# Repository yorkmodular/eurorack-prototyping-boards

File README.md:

## Eurorack module prototyping boards

A range of boards to aid the design and construction of Eurorack modules - inspired by the 'perma proto-boards' offered by the likes of AdaFruit et.al.

Three sizes are offered:

- `small` is roughly equivalent to a mini 170pt breadboard. However, unlike mini breadboards, these do have power rails (see below). Overall size is 57.2 x 64mm
- `medium` is equivalent to a half-size (400pt) breadboard. Overall size is 60.4 x 94.7mm
- `large` is equivalent to a full-size (800pt) breadboard. Note that this is far too large to be fitted in a typical Eurorack case although it could be used for 'desktop' style modules. Users of other formats may find it useful too. Overall size is 60.4 x 171.4mm.

These boards differ from 'traditional' prototyping boards in a couple of ways:

- They have three power rails, rather than two. One for +12V, one for -12V and one for ground.
- There are M3 mounting holes at each corner.
- There are an additional couple of ground rails at the top of the board.
- Power is provided by a 10-pin Eurorack power header.

Electrically, the rows of 5 pads are connected in the same way as a 'traditional' breadboard. I am planning to make pad-per-hole versions of these boards 
available in the near future.

## Buy via OSHPark

These boards can be ordered via OSHPark using the links below - note that I don't receive any commission for purchases made this way.

- Small: https://oshpark.com/shared_projects/MuwHRMNy
- Medium: https://oshpark.com/shared_projects/Uu3mWM4d
- Large: https://oshpark.com/shared_projects/nStSqsz1

------------

[![CC BY-SA 4.0][cc-by-sa-shield]][cc-by-sa]

This work is licensed under a
[Creative Commons Attribution-ShareAlike 4.0 International License][cc-by-sa].

[![CC BY-SA 4.0][cc-by-sa-image]][cc-by-sa]

[cc-by-sa]: http://creativecommons.org/licenses/by-sa/4.0/
[cc-by-sa-image]: https://licensebuttons.net/l/by-sa/4.0/88x31.png
[cc-by-sa-shield]: https://img.shields.io/badge/License-CC%20BY--SA%204.0-lightgrey.svg

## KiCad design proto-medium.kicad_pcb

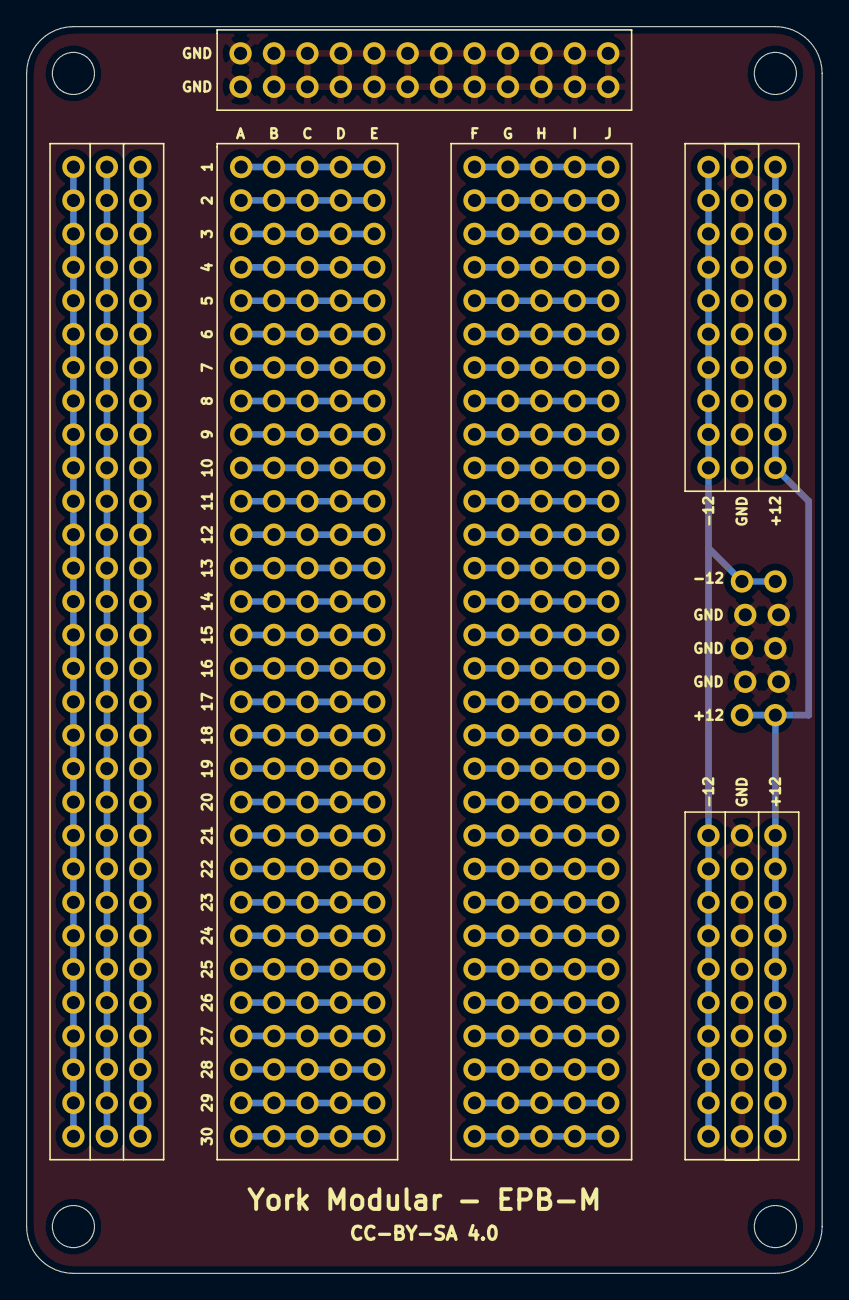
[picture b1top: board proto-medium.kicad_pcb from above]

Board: 2 copper layers, 60.5 x 94.7 mm, 26 parts (0 on the bottom side), 66 nets.

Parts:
H1, H2, H3, H4: MountingHole; MountingHole_3.2mm_M3
J1, J2, J3, J4, J5, J6, J7, J8, J9, J10, J11, J12, J13: Conn_01x30; PinHeader_1x30_P2.54mm_Vertical
J14: EURO_PWR_2x5; EURO-POWER
J15, J16, J17, J18, J19, J20: Conn_01x10; PinHeader_1x10_P2.54mm_Vertical
J21, J22: Conn_01x12; PinHeader_1x12_P2.54mm_Vertical

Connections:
+12V: J14.1, J14.2, J19.1, J19.2, J19.3, J19.4, J19.5, J19.6, J19.7, J19.8, J19.9, J19.10, J20.1, J20.2, J20.3, J20.4, J20.5, J20.6, J20.7, J20.8, J20.9, J20.10
-12V: J14.9, J14.10, J15.1, J15.2, J15.3, J15.4, J15.5, J15.6, J15.7, J15.8, J15.9, J15.10, J16.1, J16.2, J16.3, J16.4, J16.5, J16.6, J16.7, J16.8, J16.9, J16.10
GND: J14.3, J14.4, J14.5, J14.6, J14.7, J14.8, J17.1, J17.2, J17.3, J17.4, J17.5, J17.6, J17.7, J17.8, J17.9, J17.10, J18.1, J18.2, J18.3, J18.4, J18.5, J18.6, J18.7, J18.8, J18.9, J18.10, J21.1, J21.2, J21.3, J21.4, J21.5, J21.6, J21.7, J21.8, J21.9, J21.10, J21.11, J21.12, J22.1, J22.2, J22.3, J22.4, J22.5, J22.6, J22.7, J22.8, J22.9, J22.10, J22.11, J22.12
unnamed: J1.1, J2.1, J3.1, J4.1, J5.1
unnamed: J1.2, J2.2, J3.2, J4.2, J5.2
unnamed: J1.3, J2.3, J3.3, J4.3, J5.3
unnamed: J1.4, J2.4, J3.4, J4.4, J5.4
unnamed: J1.5, J2.5, J3.5, J4.5, J5.5
unnamed: J1.6, J2.6, J3.6, J4.6, J5.6
unnamed: J1.7, J2.7, J3.7, J4.7, J5.7
unnamed: J1.8, J2.8, J3.8, J4.8, J5.8
unnamed: J1.9, J2.9, J3.9, J4.9, J5.9
unnamed: J1.10, J2.10, J3.10, J4.10, J5.10
unnamed: J1.11, J2.11, J3.11, J4.11, J5.11
unnamed: J1.12, J2.12, J3.12, J4.12, J5.12
unnamed: J1.13, J2.13, J3.13, J4.13, J5.13
unnamed: J1.14, J2.14, J3.14, J4.14, J5.14
unnamed: J1.15, J2.15, J3.15, J4.15, J5.15
unnamed: J1.16, J2.16, J3.16, J4.16, J5.16
unnamed: J1.17, J2.17, J3.17, J4.17, J5.17
unnamed: J1.18, J2.18, J3.18, J4.18, J5.18
unnamed: J1.19, J2.19, J3.19, J4.19, J5.19
unnamed: J1.20, J2.20, J3.20, J4.20, J5.20
unnamed: J1.21, J2.21, J3.21, J4.21, J5.21
unnamed: J1.22, J2.22, J3.22, J4.22, J5.22
unnamed: J1.23, J2.23, J3.23, J4.23, J5.23
unnamed: J1.24, J2.24, J3.24, J4.24, J5.24
unnamed: J1.25, J2.25, J3.25, J4.25, J5.25
unnamed: J1.26, J2.26, J3.26, J4.26, J5.26
unnamed: J1.27, J2.27, J3.27, J4.27, J5.27
unnamed: J1.28, J2.28, J3.28, J4.28, J5.28
unnamed: J1.29, J2.29, J3.29, J4.29, J5.29
unnamed: J1.30, J2.30, J3.30, J4.30, J5.30
unnamed: J6.1, J7.1, J8.1, J9.1, J10.1
unnamed: J6.2, J7.2, J8.2, J9.2, J10.2
unnamed: J6.3, J7.3, J8.3, J9.3, J10.3
unnamed: J6.4, J7.4, J8.4, J9.4, J10.4
unnamed: J6.5, J7.5, J8.5, J9.5, J10.5
unnamed: J6.6, J7.6, J8.6, J9.6, J10.6
unnamed: J6.7, J7.7, J8.7, J9.7, J10.7
unnamed: J6.8, J7.8, J8.8, J9.8, J10.8
unnamed: J6.9, J7.9, J8.9, J9.9, J10.9
unnamed: J6.10, J7.10, J8.10, J9.10, J10.10
unnamed: J6.11, J7.11, J8.11, J9.11, J10.11
unnamed: J6.12, J7.12, J8.12, J9.12, J10.12
unnamed: J6.13, J7.13, J8.13, J9.13, J10.13
unnamed: J6.14, J7.14, J8.14, J9.14, J10.14
unnamed: J6.15, J7.15, J8.15, J9.15, J10.15
unnamed: J6.16, J7.16, J8.16, J9.16, J10.16
unnamed: J6.17, J7.17, J8.17, J9.17, J10.17
unnamed: J6.18, J7.18, J8.18, J9.18, J10.18
unnamed: J6.19, J7.19, J8.19, J9.19, J10.19
unnamed: J6.20, J7.20, J8.20, J9.20, J10.20
unnamed: J6.21, J7.21, J8.21, J9.21, J10.21
unnamed: J6.22, J7.22, J8.22, J9.22, J10.22
unnamed: J6.23, J7.23, J8.23, J9.23, J10.23
unnamed: J6.24, J7.24, J8.24, J9.24, J10.24
unnamed: J6.25, J7.25, J8.25, J9.25, J10.25
unnamed: J6.26, J7.26, J8.26, J9.26, J10.26
unnamed: J6.27, J7.27, J8.27, J9.27, J10.27
unnamed: J6.28, J7.28, J8.28, J9.28, J10.28
unnamed: J6.29, J7.29, J8.29, J9.29, J10.29
unnamed: J6.30, J7.30, J8.30, J9.30, J10.30
unnamed: J11.1, J11.2, J11.3, J11.4, J11.5, J11.6, J11.7, J11.8, J11.9, J11.10, J11.11, J11.12, J11.13, J11.14, J11.15, J11.16, J11.17, J11.18, J11.19, J11.20, J11.21, J11.22, J11.23, J11.24, J11.25, J11.26, J11.27, J11.28, J11.29, J11.30
unnamed: J12.1, J12.2, J12.3, J12.4, J12.5, J12.6, J12.7, J12.8, J12.9, J12.10, J12.11, J12.12, J12.13, J12.14, J12.15, J12.16, J12.17, J12.18, J12.19, J12.20, J12.21, J12.22, J12.23, J12.24, J12.25, J12.26, J12.27, J12.28, J12.29, J12.30
unnamed: J13.1, J13.2, J13.3, J13.4, J13.5, J13.6, J13.7, J13.8, J13.9, J13.10, J13.11, J13.12, J13.13, J13.14, J13.15, J13.16, J13.17, J13.18, J13.19, J13.20, J13.21, J13.22, J13.23, J13.24, J13.25, J13.26, J13.27, J13.28, J13.29, J13.30

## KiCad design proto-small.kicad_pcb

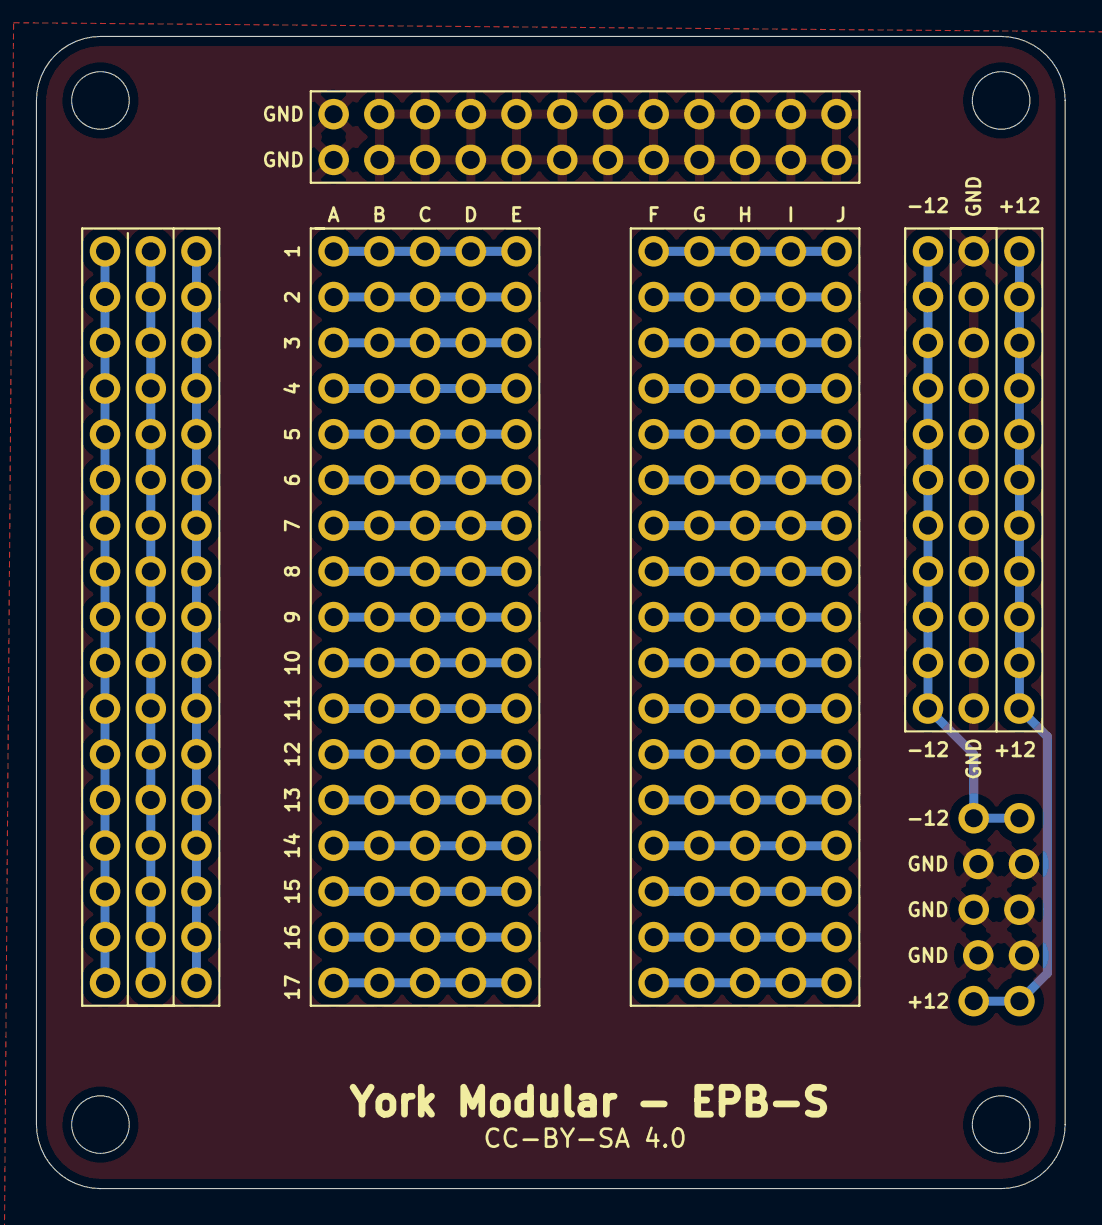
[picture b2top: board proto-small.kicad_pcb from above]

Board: 2 copper layers, 57.2 x 64.0 mm, 23 parts (0 on the bottom side), 40 nets.

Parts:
H1, H2, H3, H4: MountingHole; MountingHole_3.2mm_M3
J1, J2, J3: Conn_01x11; PinHeader_1x11_P2.54mm_Vertical
J4, J5, J6, J7, J8, J9, J10, J11, J12, J14, J15, J16, J17: Conn_01x17; PinHeader_1x17_P2.54mm_Vertical
J13: EURO_PWR_2x5; EURO-POWER
J18, J19: Conn_01x12; PinHeader_1x12_P2.54mm_Vertical

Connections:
+12V: J3.1, J3.2, J3.3, J3.4, J3.5, J3.6, J3.7, J3.8, J3.9, J3.10, J3.11, J13.1, J13.2
-12V: J1.1, J1.2, J1.3, J1.4, J1.5, J1.6, J1.7, J1.8, J1.9, J1.10, J1.11, J13.9, J13.10
GND: J2.1, J2.2, J2.3, J2.4, J2.5, J2.6, J2.7, J2.8, J2.9, J2.10, J2.11, J13.3, J13.4, J13.5, J13.6, J13.7, J13.8, J18.1, J18.2, J18.3, J18.4, J18.5, J18.6, J18.7, J18.8, J18.9, J18.10, J18.11, J18.12, J19.1, J19.2, J19.3, J19.4, J19.5, J19.6, J19.7, J19.8, J19.9, J19.10, J19.11, J19.12
unnamed: J4.1, J5.1, J6.1, J7.1, J8.1
unnamed: J4.2, J5.2, J6.2, J7.2, J8.2
unnamed: J4.3, J5.3, J6.3, J7.3, J8.3
unnamed: J4.4, J5.4, J6.4, J7.4, J8.4
unnamed: J4.5, J5.5, J6.5, J7.5, J8.5
unnamed: J4.6, J5.6, J6.6, J7.6, J8.6
unnamed: J4.7, J5.7, J6.7, J7.7, J8.7
unnamed: J4.8, J5.8, J6.8, J7.8, J8.8
unnamed: J4.9, J5.9, J6.9, J7.9, J8.9
unnamed: J4.10, J5.10, J6.10, J7.10, J8.10
unnamed: J4.11, J5.11, J6.11, J7.11, J8.11
unnamed: J4.12, J5.12, J6.12, J7.12, J8.12
unnamed: J4.13, J5.13, J6.13, J7.13, J8.13
unnamed: J4.14, J5.14, J6.14, J7.14, J8.14
unnamed: J4.15, J5.15, J6.15, J7.15, J8.15
unnamed: J4.16, J5.16, J6.16, J7.16, J8.16
unnamed: J4.17, J5.17, J6.17, J7.17, J8.17
unnamed: J9.1, J10.1, J11.1, J12.1, J14.1
unnamed: J9.2, J10.2, J11.2, J12.2, J14.2
unnamed: J9.3, J10.3, J11.3, J12.3, J14.3
unnamed: J9.4, J10.4, J11.4, J12.4, J14.4
unnamed: J9.5, J10.5, J11.5, J12.5, J14.5
unnamed: J9.6, J10.6, J11.6, J12.6, J14.6
unnamed: J9.7, J10.7, J11.7, J12.7, J14.7
unnamed: J9.8, J10.8, J11.8, J12.8, J14.8
unnamed: J9.9, J10.9, J11.9, J12.9, J14.9
unnamed: J9.10, J10.10, J11.10, J12.10, J14.10
unnamed: J9.11, J10.11, J11.11, J12.11, J14.11
unnamed: J9.12, J10.12, J11.12, J12.12, J14.12
unnamed: J9.13, J10.13, J11.13, J12.13, J14.13
unnamed: J9.14, J10.14, J11.14, J12.14, J14.14
unnamed: J9.15, J10.15, J11.15, J12.15, J14.15
unnamed: J9.16, J10.16, J11.16, J12.16, J14.16
unnamed: J9.17, J10.17, J11.17, J12.17, J14.17
unnamed: J15.1, J15.2, J15.3, J15.4, J15.5, J15.6, J15.7, J15.8, J15.9, J15.10, J15.11, J15.12, J15.13, J15.14, J15.15, J15.16, J15.17
unnamed: J16.1, J16.2, J16.3, J16.4, J16.5, J16.6, J16.7, J16.8, J16.9, J16.10, J16.11, J16.12, J16.13, J16.14, J16.15, J16.16, J16.17
unnamed: J17.1, J17.2, J17.3, J17.4, J17.5, J17.6, J17.7, J17.8, J17.9, J17.10, J17.11, J17.12, J17.13, J17.14, J17.15, J17.16, J17.17

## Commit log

2022-06-05 Add files via upload
    KiCAD PCB files for small, medium and large boards
2022-06-05 Create LICENSE
2022-06-05 Add files via upload
    Board image files
